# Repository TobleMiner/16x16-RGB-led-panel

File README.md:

16x16 LED matrix board
======================

This board is a carrier for small 1x1mm RGB LEDs. It connects pin 1 of
each LED column and the remaining pins of each row together, exposing them
via BGA-style contact pads at the bottom side of the PCB.  
The board has been designed for use with
[this](https://github.com/TobleMiner/RGB-led-nametag) project. However it
is fairly generic and could most certainly be used in your own projects,
too.

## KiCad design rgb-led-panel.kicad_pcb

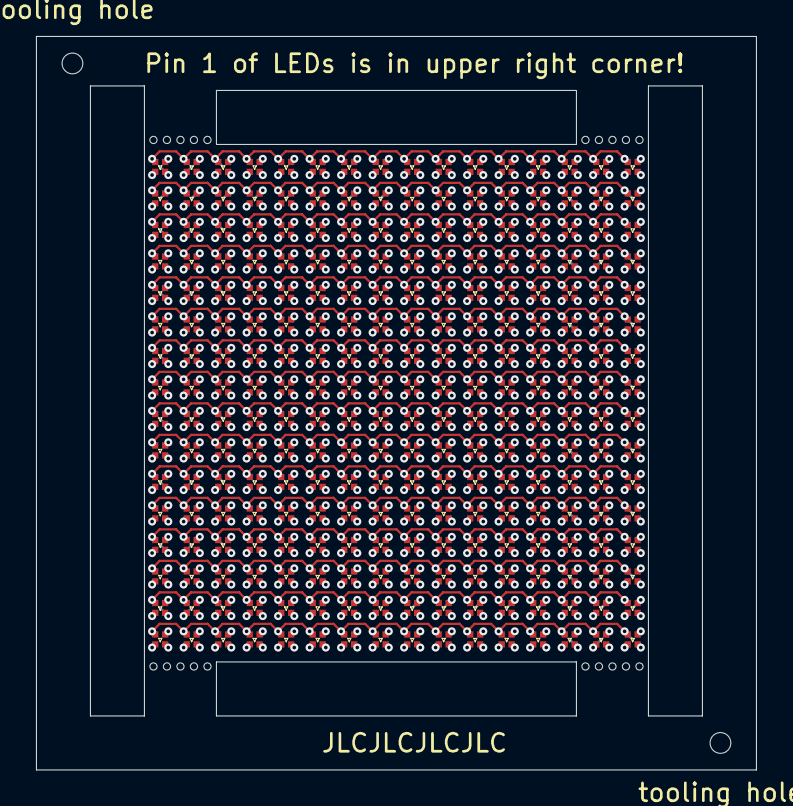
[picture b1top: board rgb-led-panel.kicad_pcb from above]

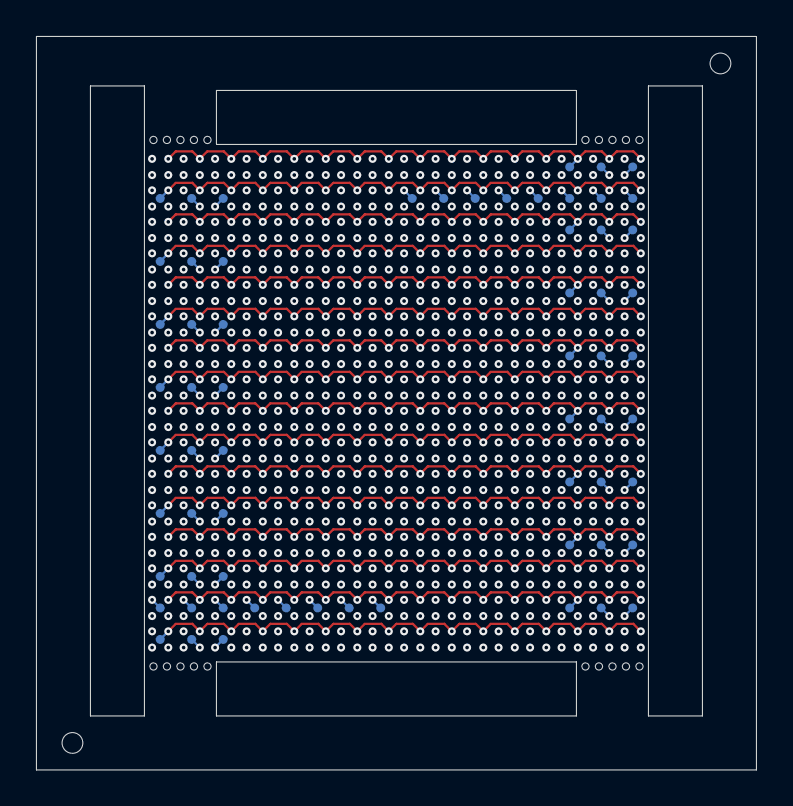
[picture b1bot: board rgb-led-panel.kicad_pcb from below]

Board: 4 copper layers, 40.0 x 40.8 mm, 322 parts (64 on the bottom side), 64 nets.

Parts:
D1, D2, D3, D4, D5, D6, D7, D8, D9, D10, D11, D12, D13, D14, D15, D16, D17, D18, D19, D20, D21, D22, D23, D24, D25, D26, D27, D28, D29, D30, D31, D32, D33, D34, D35, D36, D37, D38, D39, D40, D41, D42, D43, D44, D45, D46, D47, D48, D49, D50, D51, D52, D53, D54, D55, D56, D57, D58, D59, D60, D61, D62, D63, D64, D65, D66, D67, D68, D69, D70, D71, D72, D73, D74, D75, D76, D77, D78, D79, D80, D81, D82, D83, D84, D85, D86, D87, D88, D89, D90, D91, D92, D93, D94, D95, D96, D97, D98, D99, D100, D101, D102, D103, D104, D105, D106, D107, D108, D109, D110, D111, D112, D113, D114, D115, D116, D117, D118, D119, D120, D121, D122, D123, D124, D125, D126, D127, D128, D129, D130, D131, D132, D133, D134, D135, D136, D137, D138, D139, D140, D141, D142, D143, D144, D145, D146, D147, D148, D149, D150, D151, D152, D153, D154, D155, D156, D157, D158, D159, D160, D161, D162, D163, D164, D165, D166, D167, D168, D169, D170, D171, D172, D173, D174, D175, D176, D177, D178, D179, D180, D181, D182, D183, D184, D185, D186, D187, D188, D189, D190, D191, D192, D193, D194, D195, D196, D197, D198, D199, D200, D201, D202, D203, D204, D205, D206, D207, D208, D209, D210, D211, D212, D213, D214, D215, D216, D217, D218, D219, D220, D221, D222, D223, D224, D225, D226, D227, D228, D229, D230, D231, D232, D233, D234, D235, D236, D237, D238, D239, D240, D241, D242, D243, D244, D245, D246, D247, D248, D249, D250, D251, D252, D253, D254, D255, D256: LED_ARGB; MHPA0808RGBDT
H1, H2: ToolingHole; ToolingHole_JLCSMT
TP1: A1; TestPoint_0.5mm
TP2: A2; TestPoint_0.5mm
TP3: A3; TestPoint_0.5mm
TP4: A4; TestPoint_0.5mm
TP5: A5; TestPoint_0.5mm
TP6: A6; TestPoint_0.5mm
TP7: A7; TestPoint_0.5mm
TP8: A8; TestPoint_0.5mm
TP9: A9; TestPoint_0.5mm
TP10: A10; TestPoint_0.5mm
TP11: A11; TestPoint_0.5mm
TP12: A12; TestPoint_0.5mm
TP13: A13; TestPoint_0.5mm
TP14: A14; TestPoint_0.5mm
TP15: A15; TestPoint_0.5mm
TP16: A16; TestPoint_0.5mm
TP17, TP18, TP19, TP20, TP21, TP22, TP23, TP24, TP25, TP26, TP27, TP28, TP29, TP30, TP31, TP32: R1; TestPoint_0.5mm
TP33, TP34, TP35, TP36, TP37, TP38, TP39, TP40, TP41, TP42, TP43, TP44, TP45, TP46, TP47, TP48: G1; TestPoint_0.5mm
TP49, TP50, TP51, TP52, TP53, TP54, TP55, TP56, TP57, TP58, TP59, TP60, TP61, TP62, TP63, TP64: B1; TestPoint_0.5mm

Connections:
/Leds/C1/ANODE: D1.1, D2.1, D3.1, D4.1, D5.1, D6.1, D7.1, D8.1, D9.1, D10.1, D11.1, D12.1, D13.1, D14.1, D15.1, D16.1, TP1.1
/Leds/C1/B1: D1.4, TP49.1
/Leds/C1/B2: D3.4, TP50.1
/Leds/C1/B3: D5.4, TP51.1
/Leds/C1/B4: D7.4, TP52.1
/Leds/C1/B5: D9.4, TP53.1
/Leds/C1/B6: D11.4, TP54.1
/Leds/C1/B7: D13.4, TP55.1
/Leds/C1/B8: D15.4, TP56.1
/Leds/C1/B9: D2.4, TP57.1
/Leds/C1/B10: D4.4, TP58.1
/Leds/C1/B11: D6.4, TP59.1
/Leds/C1/B12: D8.4, TP60.1
/Leds/C1/B13: D10.4, TP61.1
/Leds/C1/B14: D12.4, TP62.1
/Leds/C1/B15: D14.4, TP63.1
/Leds/C1/B16: D16.4, TP64.1
/Leds/C1/G1: D1.3, TP33.1
/Leds/C1/G2: D3.3, TP34.1
/Leds/C1/G3: D5.3, TP35.1
/Leds/C1/G4: D7.3, TP36.1
/Leds/C1/G5: D9.3, TP37.1
/Leds/C1/G6: D11.3, TP38.1
/Leds/C1/G7: D13.3, TP39.1
/Leds/C1/G8: D15.3, TP40.1
/Leds/C1/G9: D2.3, TP41.1
/Leds/C1/G10: D4.3, TP42.1
/Leds/C1/G11: D6.3, TP43.1
/Leds/C1/G12: D8.3, TP44.1
/Leds/C1/G13: D10.3, TP45.1
/Leds/C1/G14: D12.3, TP46.1
/Leds/C1/G15: D14.3, TP47.1
/Leds/C1/G16: D16.3, TP48.1
/Leds/C1/R1: D1.2, TP17.1
/Leds/C1/R2: D3.2, TP18.1
/Leds/C1/R3: D5.2, TP19.1
/Leds/C1/R4: D7.2, TP20.1
/Leds/C1/R5: D9.2, TP21.1
/Leds/C1/R6: D11.2, TP22.1
/Leds/C1/R7: D13.2, TP23.1
/Leds/C1/R8: D15.2, TP24.1
/Leds/C1/R9: D2.2, TP25.1
/Leds/C1/R10: D4.2, TP26.1
/Leds/C1/R11: D6.2, TP27.1
/Leds/C1/R12: D8.2, TP28.1
/Leds/C1/R13: D10.2, TP29.1
/Leds/C1/R14: D12.2, TP30.1
/Leds/C1/R15: D14.2, TP31.1
/Leds/C1/R16: D16.2, TP32.1
/Leds/C2/ANODE: D17.1, D18.1, D19.1, D20.1, D21.1, D22.1, D23.1, D24.1, D25.1, D26.1, D27.1, D28.1, D29.1, D30.1, D31.1, D32.1, TP2.1
/Leds/C3/ANODE: D33.1, D34.1, D35.1, D36.1, D37.1, D38.1, D39.1, D40.1, D41.1, D42.1, D43.1, D44.1, D45.1, D46.1, D47.1, D48.1, TP3.1
/Leds/C4/ANODE: D49.1, D50.1, D51.1, D52.1, D53.1, D54.1, D55.1, D56.1, D57.1, D58.1, D59.1, D60.1, D61.1, D62.1, D63.1, D64.1, TP4.1
/Leds/C5/ANODE: D65.1, D66.1, D67.1, D68.1, D69.1, D70.1, D71.1, D72.1, D73.1, D74.1, D75.1, D76.1, D77.1, D78.1, D79.1, D80.1, TP5.1
/Leds/C6/ANODE: D81.1, D82.1, D83.1, D84.1, D85.1, D86.1, D87.1, D88.1, D89.1, D90.1, D91.1, D92.1, D93.1, D94.1, D95.1, D96.1, TP6.1
/Leds/C7/ANODE: D241.1, D242.1, D243.1, D244.1, D245.1, D246.1, D247.1, D248.1, D249.1, D250.1, D251.1, D252.1, D253.1, D254.1, D255.1, D256.1, TP7.1
/Leds/C8/ANODE: D97.1, D98.1, D99.1, D100.1, D101.1, D102.1, D103.1, D104.1, D105.1, D106.1, D107.1, D108.1, D109.1, D110.1, D111.1, D112.1, TP8.1
/Leds/C9/ANODE: D113.1, D114.1, D115.1, D116.1, D117.1, D118.1, D119.1, D120.1, D121.1, D122.1, D123.1, D124.1, D125.1, D126.1, D127.1, D128.1, TP9.1
/Leds/C10/ANODE: D129.1, D130.1, D131.1, D132.1, D133.1, D134.1, D135.1, D136.1, D137.1, D138.1, D139.1, D140.1, D141.1, D142.1, D143.1, D144.1, TP10.1
/Leds/C11/ANODE: D145.1, D146.1, D147.1, D148.1, D149.1, D150.1, D151.1, D152.1, D153.1, D154.1, D155.1, D156.1, D157.1, D158.1, D159.1, D160.1, TP11.1
/Leds/C12/ANODE: D161.1, D162.1, D163.1, D164.1, D165.1, D166.1, D167.1, D168.1, D169.1, D170.1, D171.1, D172.1, D173.1, D174.1, D175.1, D176.1, TP12.1
/Leds/C13/ANODE: D177.1, D178.1, D179.1, D180.1, D181.1, D182.1, D183.1, D184.1, D185.1, D186.1, D187.1, D188.1, D189.1, D190.1, D191.1, D192.1, TP13.1
/Leds/C14/ANODE: D193.1, D194.1, D195.1, D196.1, D197.1, D198.1, D199.1, D200.1, D201.1, D202.1, D203.1, D204.1, D205.1, D206.1, D207.1, D208.1, TP14.1
/Leds/C15/ANODE: D209.1, D210.1, D211.1, D212.1, D213.1, D214.1, D215.1, D216.1, D217.1, D218.1, D219.1, D220.1, D221.1, D222.1, D223.1, D224.1, TP15.1
/Leds/C16/ANODE: D225.1, D226.1, D227.1, D228.1, D229.1, D230.1, D231.1, D232.1, D233.1, D234.1, D235.1, D236.1, D237.1, D238.1, D239.1, D240.1, TP16.1

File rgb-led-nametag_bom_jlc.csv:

"Comment","Designator","Footprint","LCSC Part #"
"LED_ARGB","D1,D3,D5,D7,D9,D11,D13,D15,D2,D4,D6,D8,D10,D12,D14,D16,D17,D19,D21,D23,D25,D27,D29,D31,D18,D20,D22,D24,D26,D28,D30,D32,D33,D35,D37,D39,D41,D43,D45,D47,D34,D36,D38,D40,D42,D44,D46,D48,D49,D51,D53,D55,D57,D59,D61,D63,D50,D52,D54,D56,D58,D60,D62,D64,D65,D67,D69,D71,D73,D75,D77,D79,D66,D68,D70,D72,D74,D76,D78,D80,D81,D83,D85,D87,D89,D91,D93,D95,D82,D84,D86,D88,D90,D92,D94,D96,D97,D99,D101,D103,D105,D107,D109,D111,D98,D100,D102,D104,D106,D108,D110,D112,D113,D115,D117,D119,D121,D123,D125,D127,D114,D116,D118,D120,D122,D124,D126,D128,D129,D131,D133,D135,D137,D139,D141,D143,D130,D132,D134,D136,D138,D140,D142,D144,D145,D147,D149,D151,D153,D155,D157,D159,D146,D148,D150,D152,D154,D156,D158,D160,D161,D163,D165,D167,D169,D171,D173,D175,D162,D164,D166,D168,D170,D172,D174,D176,D177,D179,D181,D183,D185,D187,D189,D191,D178,D180,D182,D184,D186,D188,D190,D192,D193,D195,D197,D199,D201,D203,D205,D207,D194,D196,D198,D200,D202,D204,D206,D208,D209,D211,D213,D215,D217,D219,D221,D223,D210,D212,D214,D216,D218,D220,D222,D224,D225,D227,D229,D231,D233,D235,D237,D239,D226,D228,D230,D232,D234,D236,D238,D240,D241,D243,D245,D247,D249,D251,D253,D255,D242,D244,D246,D248,D250,D252,D254,D256","MHPA0808RGBDT","C404279"

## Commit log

2021-11-28 Layout 16x16 RGB panel
2021-12-29 Add rails to protect left and right pcb edges in manufacturing
    Without the rails the left and right edges of the LED PCB can end up with
    burrs from other PCBs in the same panel.
2021-12-30 Add solder paste definition to BGA contact pads
2021-12-30 Use new contact point footprint
2022-01-15 Add license
2022-01-15 Add readme
2022-01-15 Add screenshot of PCB front side to readme
